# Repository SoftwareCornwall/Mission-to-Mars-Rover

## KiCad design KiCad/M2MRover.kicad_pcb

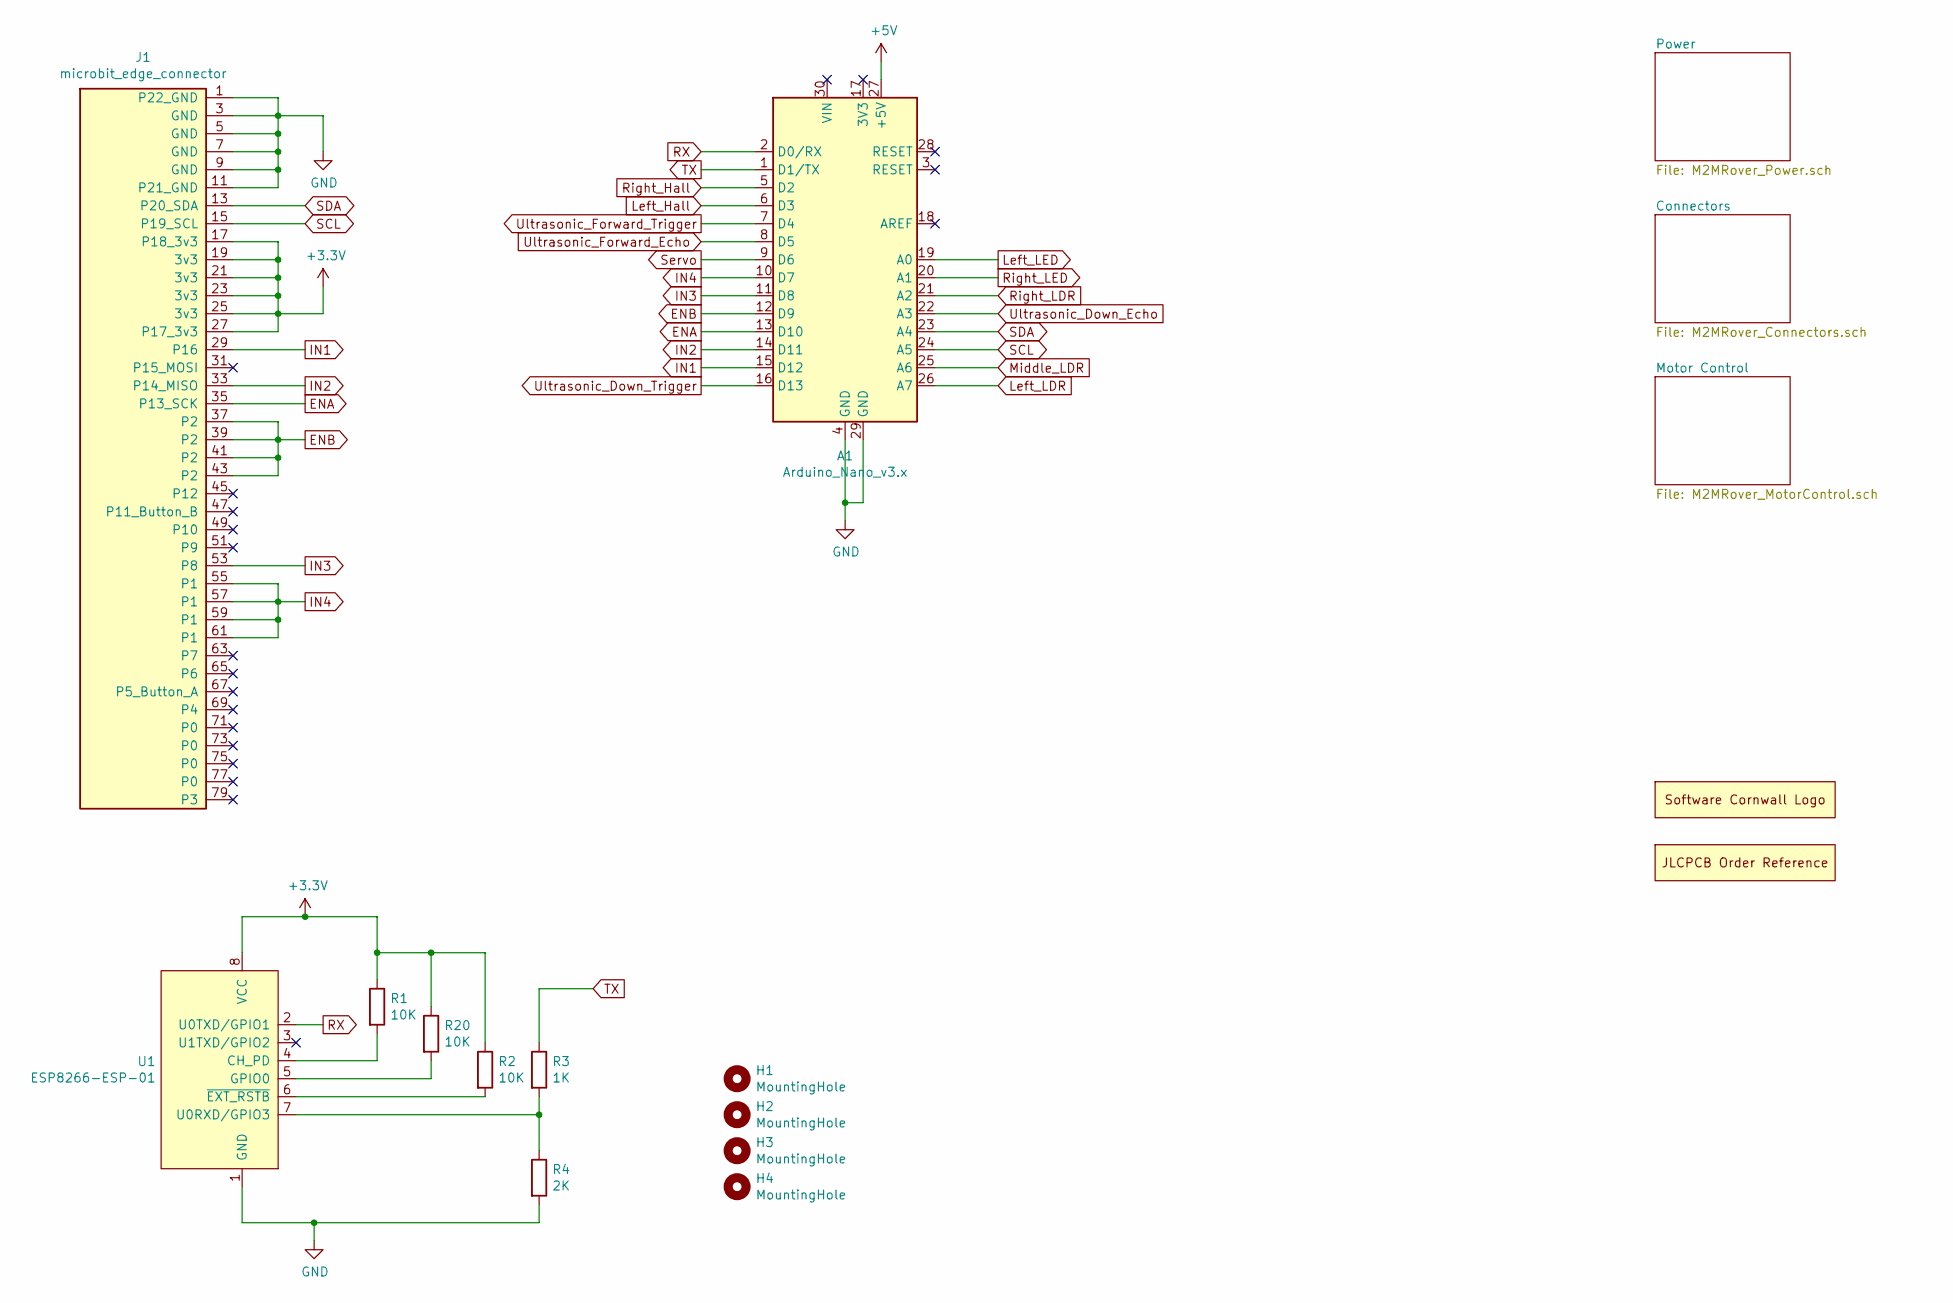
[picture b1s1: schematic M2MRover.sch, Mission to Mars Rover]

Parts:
A1: Arduino_Nano_v3.x; Arduino_Nano
H1, H2, H3, H4: MountingHole; MountingHole_2.7mm_Pad
J1: microbit_edge_connector; 4UCON_10156_B3_Horizontal
LOGO1: Software_Cornwall_Logo; SoftwareCornwallLogo
ORDERNO1: JLCPCB_Order_Number; JLCPCBOrderNumber
R1, R2, R20: 10K; R_0805_2012Metric_Pad1.15x1.40mm_HandSolder
R3: 1K; R_0805_2012Metric_Pad1.15x1.40mm_HandSolder
R4: 2K; R_0805_2012Metric_Pad1.15x1.40mm_HandSolder
U1: ESP8266-ESP-01; PinSocket_2x04_P2.54mm_Vertical

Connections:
+3V3: J1.17 (P18_3v3), J1.19 (3v3), J1.21 (3v3), J1.23 (3v3), J1.25 (3v3), J1.27 (P17_3v3), R1.1, R2.1, R20.1, U1.8 (VCC); also elsewhere on the board
+5V: A1.27 (+5V); also elsewhere on the board
ENA: A1.13 (D10), J1.35 (P13_SCK); also elsewhere on the board
ENB: A1.12 (D9), J1.37 (P2), J1.39 (P2), J1.41 (P2), J1.43 (P2); also elsewhere on the board
GND: A1.4 (GND), A1.29 (GND), J1.1 (P22_GND), J1.3 (GND), J1.5 (GND), J1.7 (GND), J1.9 (GND), J1.11 (P21_GND), R4.2, U1.1 (GND); also elsewhere on the board
IN1: A1.15 (D12), J1.29 (P16); also elsewhere on the board
IN2: A1.14 (D11), J1.33 (P14_MISO); also elsewhere on the board
IN3: A1.11 (D8), J1.53 (P8); also elsewhere on the board
IN4: A1.10 (D7), J1.55 (P1), J1.57 (P1), J1.59 (P1), J1.61 (P1); also elsewhere on the board
Left_Hall: A1.6 (D3); also elsewhere on the board
Left_LDR: A1.26 (A7); also elsewhere on the board
Left_LED: A1.19 (A0); also elsewhere on the board
Middle_LDR: A1.25 (A6); also elsewhere on the board
unnamed: R1.2, U1.4 (CH_PD)
unnamed: R2.2, U1.6 (~EXT_RSTB)
unnamed: R3.2, R4.1, U1.7 (U0RXD/GPIO3)
unnamed: R20.2, U1.5 (GPIO0)
RX: A1.2 (D0/RX), U1.2 (U0TXD/GPIO1); also elsewhere on the board
Right_Hall: A1.5 (D2); also elsewhere on the board
Right_LDR: A1.21 (A2); also elsewhere on the board
Right_LED: A1.20 (A1); also elsewhere on the board
SCL: A1.24 (A5), J1.15 (P19_SCL); also elsewhere on the board
SDA: A1.23 (A4), J1.13 (P20_SDA); also elsewhere on the board
Servo: A1.9 (D6); also elsewhere on the board
TX: A1.1 (D1/TX), R3.1; also elsewhere on the board
Ultrasonic_Down_Echo: A1.22 (A3); also elsewhere on the board
Ultrasonic_Down_Trigger: A1.16 (D13); also elsewhere on the board
Ultrasonic_Forward_Echo: A1.8 (D5); also elsewhere on the board
Ultrasonic_Forward_Trigger: A1.7 (D4); also elsewhere on the board

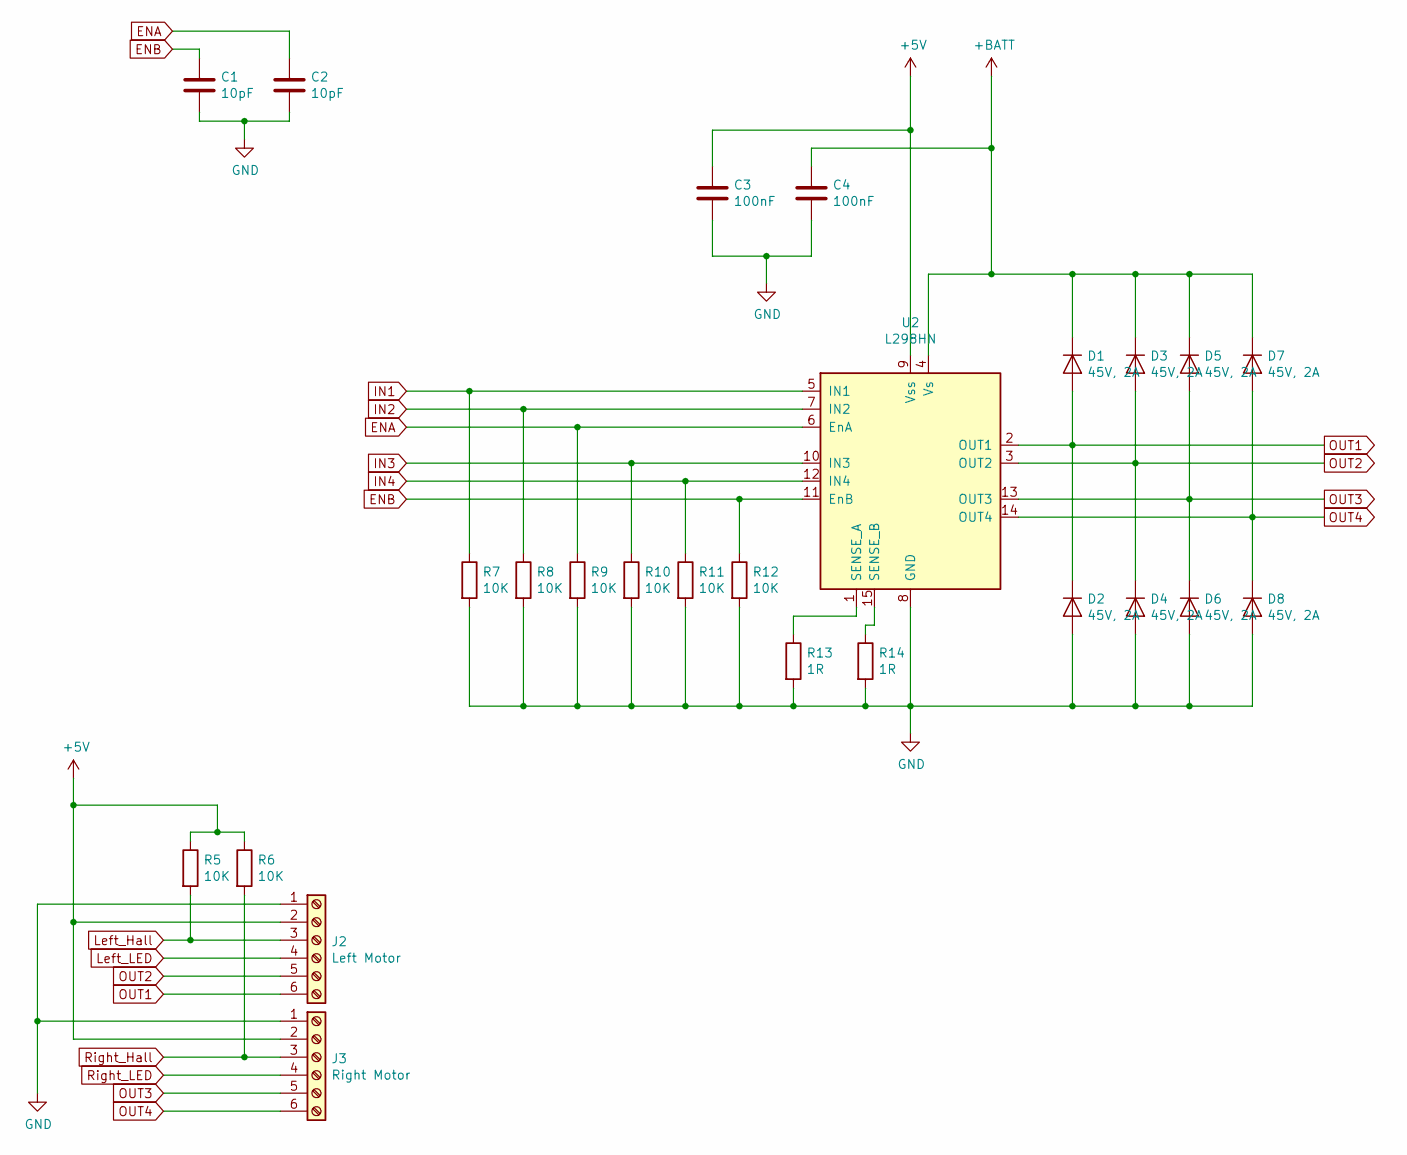
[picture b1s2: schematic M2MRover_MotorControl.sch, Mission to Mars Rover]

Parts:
C1, C2: 10pF; C_0805_2012Metric_Pad1.15x1.40mm_HandSolder
C3, C4: 100nF; C_0805_2012Metric_Pad1.15x1.40mm_HandSolder
D1, D2, D3, D4, D5, D6, D7, D8: 45V, 2A; D_SOD-123
J2: Left Motor; PinSocket_1x06_P2.54mm_Vertical
J3: Right Motor; PinSocket_1x06_P2.54mm_Vertical
R5, R6, R7, R8, R9, R10, R11, R12: 10K; R_0805_2012Metric_Pad1.15x1.40mm_HandSolder
R13, R14: 1R; R_0805_2012Metric_Pad1.15x1.40mm_HandSolder
U2: L298HN; TO-220-15_P2.54x2.54mm_StaggerOdd_Lead4.58mm_Vertical

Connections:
+5V: C3.1, J2.2, J3.2, R5.1, R6.1, U2.9 (Vss); also elsewhere on the board
+BATT: C4.1, D1.1 (K), D3.1 (K), D5.1 (K), D7.1 (K), U2.4 (Vs); also elsewhere on the board
ENA: C2.1, R9.1, U2.6 (EnA); also elsewhere on the board
ENB: C1.1, R12.1, U2.11 (EnB); also elsewhere on the board
GND: C1.2, C2.2, C3.2, C4.2, D2.2 (A), D4.2 (A), D6.2 (A), D8.2 (A), J2.1, J3.1, R7.2, R8.2, R9.2, R10.2, R11.2, R12.2, R13.2, R14.2, U2.8 (GND); also elsewhere on the board
IN1: R7.1, U2.5 (IN1); also elsewhere on the board
IN2: R8.1, U2.7 (IN2); also elsewhere on the board
IN3: R10.1, U2.10 (IN3); also elsewhere on the board
IN4: R11.1, U2.12 (IN4); also elsewhere on the board
Left_Hall: J2.3, R5.2; also elsewhere on the board
Left_LED: J2.4; also elsewhere on the board
unnamed: R13.1, U2.1 (SENSE_A)
unnamed: R14.1, U2.15 (SENSE_B)
OUT1: D1.2 (A), D2.1 (K), J2.6, U2.2 (OUT1)
OUT2: D3.2 (A), D4.1 (K), J2.5, U2.3 (OUT2)
OUT3: D5.2 (A), D6.1 (K), J3.5, U2.13 (OUT3)
OUT4: D7.2 (A), D8.1 (K), J3.6, U2.14 (OUT4)
Right_Hall: J3.3, R6.2; also elsewhere on the board
Right_LED: J3.4; also elsewhere on the board

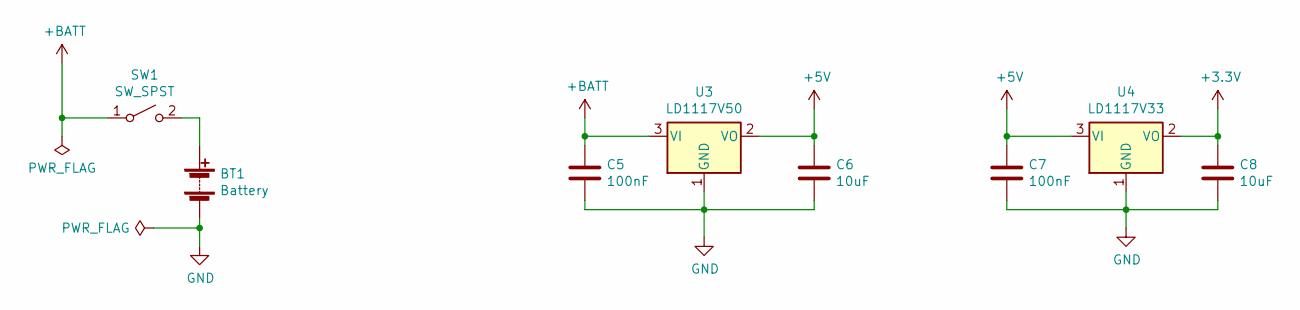
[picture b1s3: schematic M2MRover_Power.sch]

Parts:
BT1: Battery; PinHeader_1x02_P2.54mm_Vertical
C5, C7: 100nF; C_0805_2012Metric_Pad1.15x1.40mm_HandSolder
C6, C8: 10uF; C_0805_2012Metric_Pad1.15x1.40mm_HandSolder
SW1: SW_SPST; PinHeader_1x02_P2.54mm_Vertical
U3: LD1117V50; TO-220-3_Vertical
U4: LD1117V33; TO-220-3_Vertical

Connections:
+3V3: C8.1, U4.2 (VO); also elsewhere on the board
+5V: C6.1, C7.1, U3.2 (VO), U4.3 (VI); also elsewhere on the board
+BATT: C5.1, SW1.1 (A), U3.3 (VI); also elsewhere on the board
GND: BT1.2 (-), C5.2, C6.2, C7.2, C8.2, U3.1 (GND), U4.1 (GND); also elsewhere on the board
unnamed: BT1.1 (+), SW1.2 (B)

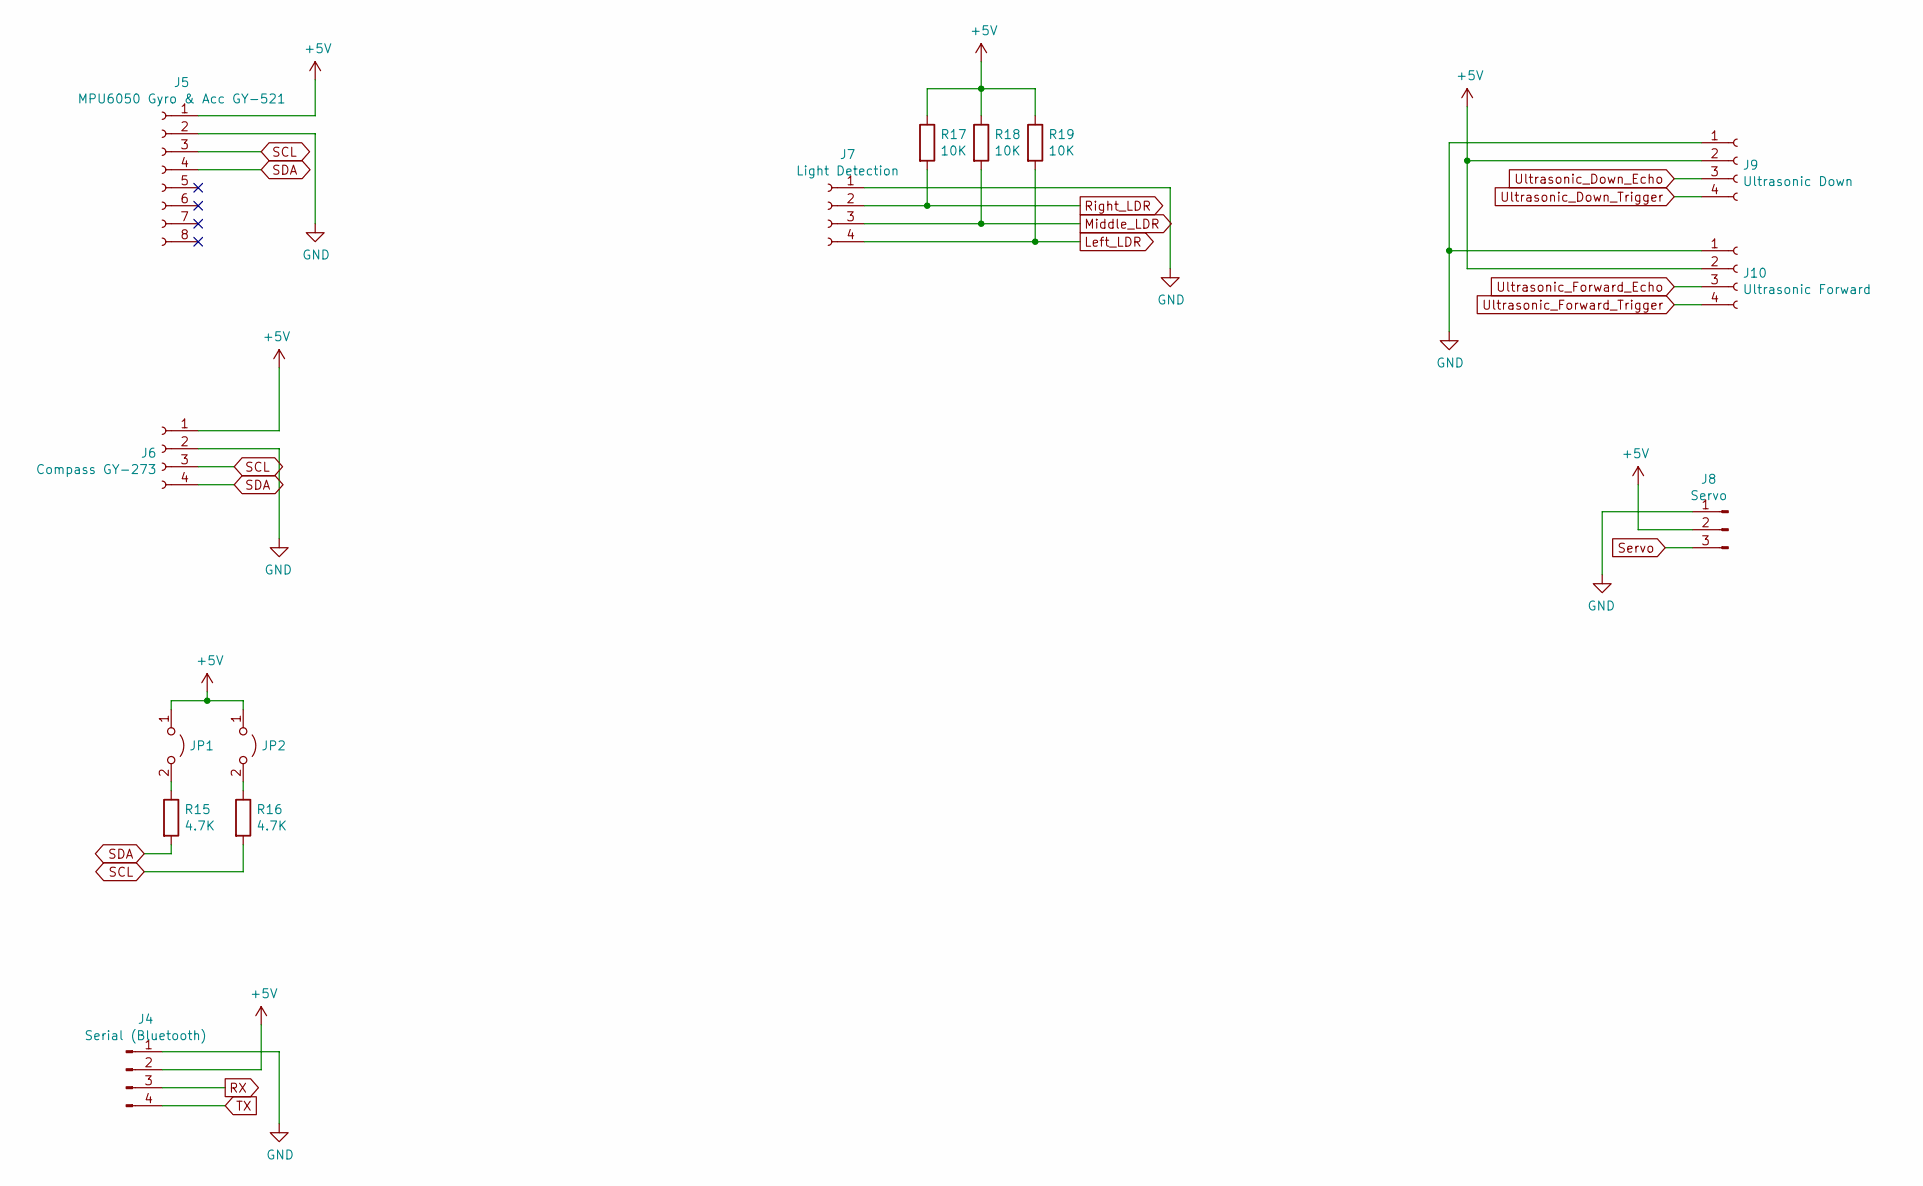
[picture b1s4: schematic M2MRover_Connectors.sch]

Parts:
J4: Serial (Bluetooth); PinHeader_1x04_P2.54mm_Vertical
J5: MPU6050 Gyro & Acc GY-521; PinSocket_1x08_P2.54mm_Vertical
J6: Compass GY-273; PinSocket_1x04_P2.54mm_Vertical
J7: Light Detection; PinSocket_1x04_P2.54mm_Vertical
J8: Servo; PinHeader_1x03_P2.54mm_Vertical
J9: Ultrasonic Down; PinSocket_1x04_P2.54mm_Vertical
J10: Ultrasonic Forward; PinSocket_1x04_P2.54mm_Vertical
JP1, JP2: Jumper_2_Open; PinHeader_1x02_P2.54mm_Vertical
R15, R16: 4.7K; R_0805_2012Metric_Pad1.15x1.40mm_HandSolder
R17, R18, R19: 10K; R_0805_2012Metric_Pad1.15x1.40mm_HandSolder

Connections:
+5V: J4.2, J5.1, J6.1, J8.2, J9.2, J10.2, JP1.1 (A), JP2.1 (A), R17.1, R18.1, R19.1; also elsewhere on the board
GND: J4.1, J5.2, J6.2, J7.1, J8.1, J9.1, J10.1; also elsewhere on the board
Left_LDR: J7.4, R19.2; also elsewhere on the board
Middle_LDR: J7.3, R18.2; also elsewhere on the board
unnamed: JP1.2 (B), R15.1
unnamed: JP2.2 (B), R16.1
RX: J4.3; also elsewhere on the board
Right_LDR: J7.2, R17.2; also elsewhere on the board
SCL: J5.3, J6.3, R16.2; also elsewhere on the board
SDA: J5.4, J6.4, R15.2; also elsewhere on the board
Servo: J8.3; also elsewhere on the board
TX: J4.4; also elsewhere on the board
Ultrasonic_Down_Echo: J9.3; also elsewhere on the board
Ultrasonic_Down_Trigger: J9.4; also elsewhere on the board
Ultrasonic_Forward_Echo: J10.3; also elsewhere on the board
Ultrasonic_Forward_Trigger: J10.4; also elsewhere on the board

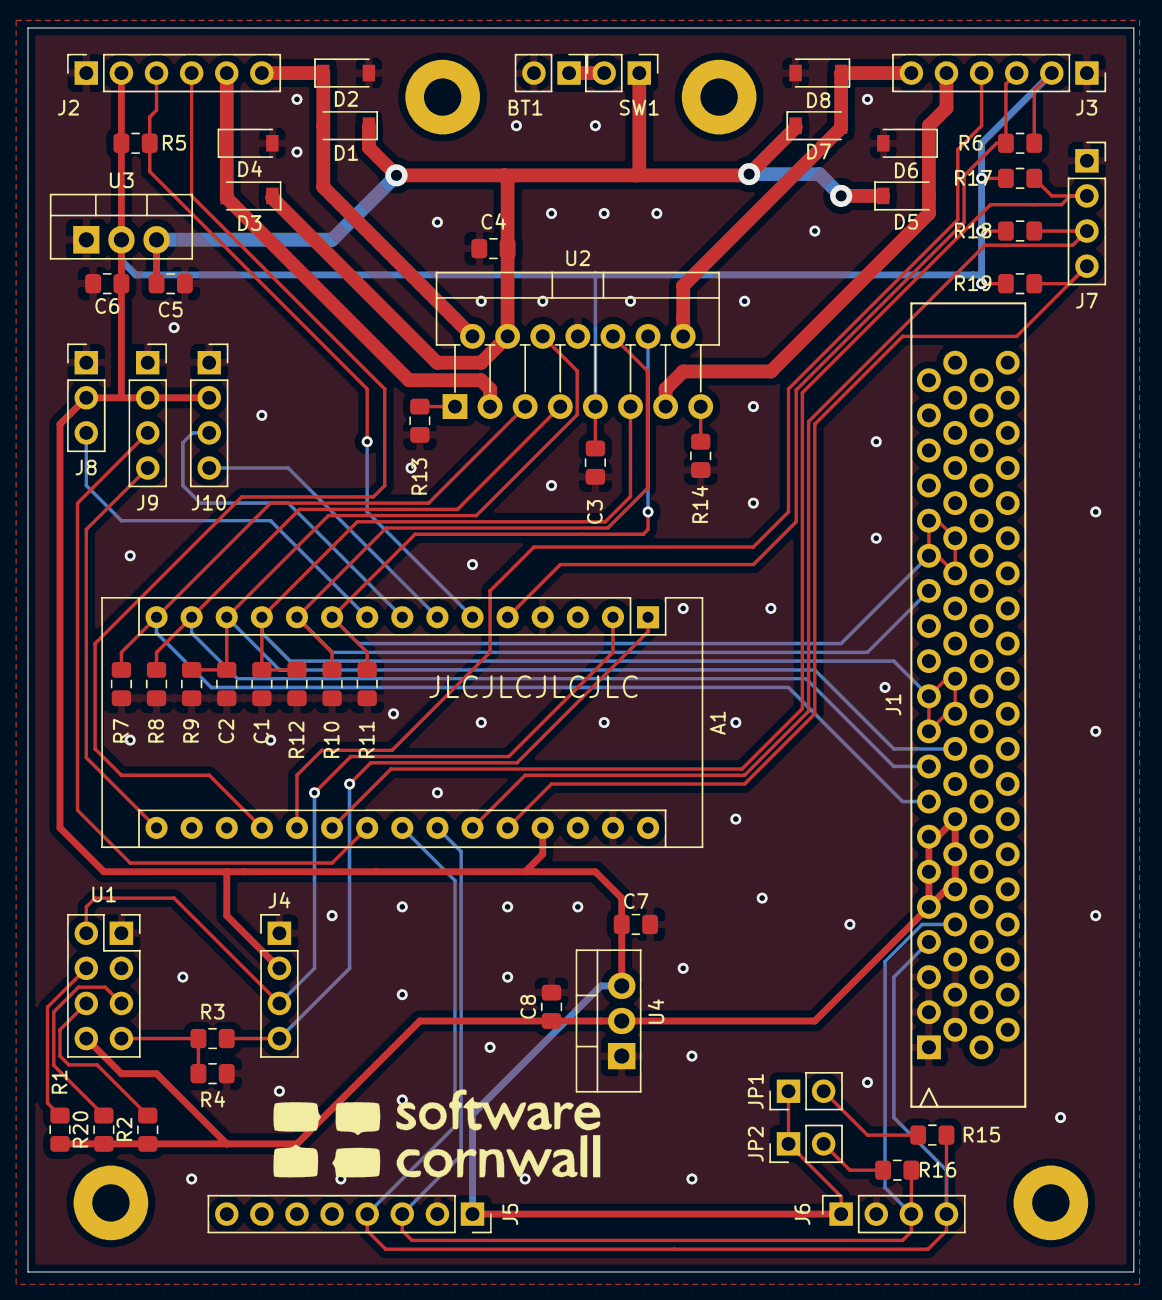
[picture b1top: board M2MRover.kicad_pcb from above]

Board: 2 copper layers, 80.0 x 90.0 mm, 61 parts (0 on the bottom side), 39 nets.

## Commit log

2019-08-20 Update issue templates
2019-08-22 Add ESP8266 submodule
2019-08-22 Update ESP8266_Modules sub-module
2019-08-23 Replace ESP8266 connector with component
2019-08-28 Add I2C pull up resistors
2019-08-28 Add capacitors to PWM output for EMC
2019-08-28 Update schematic PDF
2019-08-28 Add Software Cornwall logo to schematic
2019-08-28 Add PCB Software Cornwall logo
2019-08-30 Add initial PCB layout
2019-08-30 Update PDFs of Schematic and PCB
2019-09-01 Change 3.3V regulator to LD1117
2019-09-01 Add footprints for passive components
2019-09-01 Add passive components to PCB layout
2019-09-05 Add jumpers to I2C lines and start PCB layout
2019-09-07 Add L298 component to replace separate pcb
2019-09-12 Add L298N H-Bridge driver
2019-09-17 Add initial BOM
2019-09-22 Add footprints for diodes
2019-09-22 Updated BOM
2019-09-22 Refactor motor wiring to h-bridge
2019-09-23 Route the PCB
2019-09-23 Track everything apart from LEDs and MicroBit
2019-09-23 Track all remaining of components
2019-09-23 Add power plain on front side copper
2019-09-23 Refactor some track layouts
2019-09-23 Update PDFs with latest design
2019-09-24 Increase H-Bridge track thickness
2019-09-24 Add measurement for edge of MicroBit connector
2019-09-24 Add Software Cornwall logo to silk layer
2019-09-30 Add pull up resistor to ESP8266 GPIO0 and remove GND tracks
2019-09-30 Update BOM to decide how many chassis to build
2019-09-30 Update BOM
2019-09-30 Add component for Software Cornwall Logo
2019-09-30 Add Software Cornwall Log via symbol
2019-10-01 Move 5V regulator to stop physical clash
2019-10-01 Add JLCPCB order number to silk
2019-10-02 Generate Gerbers
2019-10-03 Add Back Mask layer
2019-10-03 Regenerate Gerber files
2019-10-03 Tidy up labels on PCB Silk layer
2019-10-03 Add zip of Gerbers set for manufacture
2019-10-06 Update BOM with RS part numbers
2019-10-15 Update BOM with ordered items
2019-12-24 Add interactive BOM
2019-12-24 Add datasheet for Schottky Diode
2019-12-24 Add information about chassis
2019-12-24 Add latest BOM updates
2019-12-24 Add Arduino hardware test project
2020-01-01 Update BOM with current status of bought parts
2020-01-03 Add code to test servos and ultrasonic sensors
2020-01-03 Add datasheets for solder
2020-01-03 Add footprint for micro:bit connector from Cool Components
2020-01-03 Change microbit connector footprint to use new custom footprint
2020-01-03 Move components near J2 & J3 to allow more room for connectors
2020-01-03 Update Gerbers
2020-01-05 Add zipped gerbers
2020-07-26 Add Arduino Mars Rover library
2020-07-26 Move hardware test into Arduino library
2020-07-26 Fix missing file extension on Diode datasheet
2020-07-27 Add initial iteration of handouts
2020-07-27 Add simple circuit diagram
2020-07-28 Add Story 7 breadboard file
2020-07-28 Update the resistor values in the handouts
2020-07-28 Correct name for Story 5 handout
2020-07-28 Add story breadboard images to Rover Information
2020-07-28 Add breadboard diagrams for stories 9, 10 & 11
2020-07-28 Add images of Arduino Nanos to Pins page
2020-07-28 Updatte Rover Information with front page and PCB as Breadboard
2020-09-12 Add support for V1 Rovers in Arduino library
2021-06-16 Add MicroBit motors test
2021-07-05 Add updated documentation
